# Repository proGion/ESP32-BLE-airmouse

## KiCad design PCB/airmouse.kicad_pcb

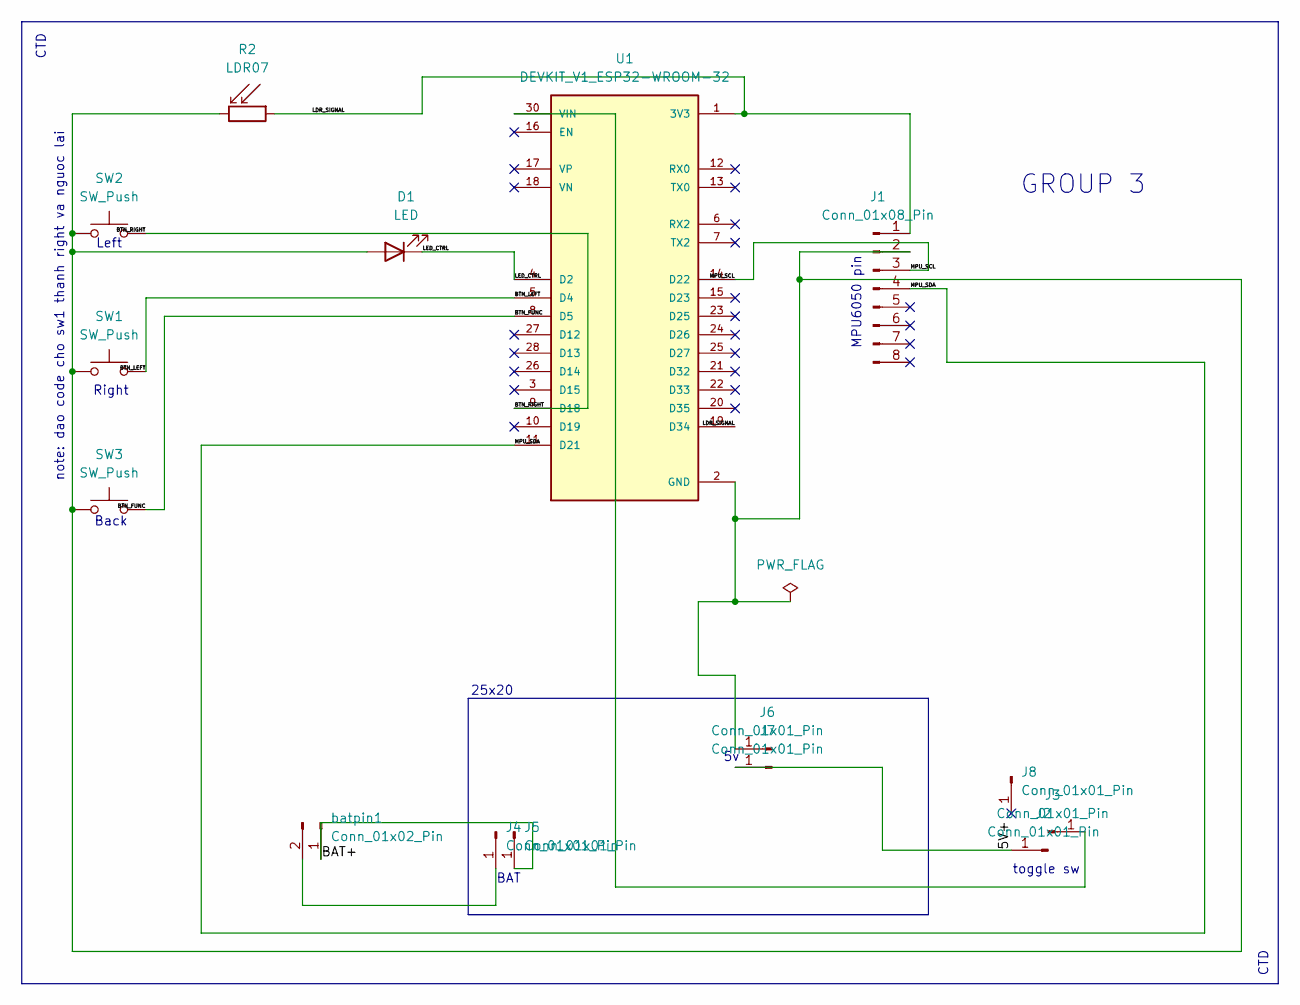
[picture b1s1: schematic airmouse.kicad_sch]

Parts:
D1: LED; LED_D5.0mm
J1: Conn_01x08_Pin; PinHeader_1x08_P2.54mm_Vertical
J2, J3, J4, J5, J6, J7, J8: Conn_01x01_Pin; PinHeader_1x01_P2.54mm_Vertical
R2: LDR07; R_LDR_5.1x4.3mm_P3.4mm_Vertical
SW1, SW2, SW3: SW_Push; SW_PUSH_6mm_H9.5mm
U1: DEVKIT_V1_ESP32-WROOM-32; MODULE_DEVKIT_V1_ESP32-WROOM-32
batpin1: Conn_01x02_Pin; PinHeader_1x02_P2.54mm_Vertical

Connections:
/5V+: J2.1 (Pin_1_1), J7.1 (Pin_1_1)
/BAT+: J5.1 (Pin_1_1), batpin1.1
/BTN_FUNC: SW3.2, U1.8 (D5)
/BTN_LEFT: SW1.2, U1.5 (D4)
/BTN_RIGHT: SW2.2, U1.9 (D18)
/LDR_SIGNAL: J1.1, R2.1, U1.1 (3V3), U1.19 (D34)
/LED_CTRL: D1.1 (K), U1.4 (D2)
/MPU_SCL: J1.3, U1.14 (D22)
/MPU_SDA: J1.4, U1.11 (D21)
GND: D1.2 (A), J1.2, J6.1 (Pin_1_1), R2.2, SW1.1, SW2.1, SW3.1, U1.2 (GND), U1.29 (GND)
unnamed: J3.1 (Pin_1_1), U1.30 (VIN)
unnamed: J4.1 (Pin_1_1), batpin1.2

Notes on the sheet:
MPU6050 pin
Left
CTD
note: dao code cho sw1 thanh right va nguoc lai
BAT
25x20
toggle sw
Right
GROUP 3
Back

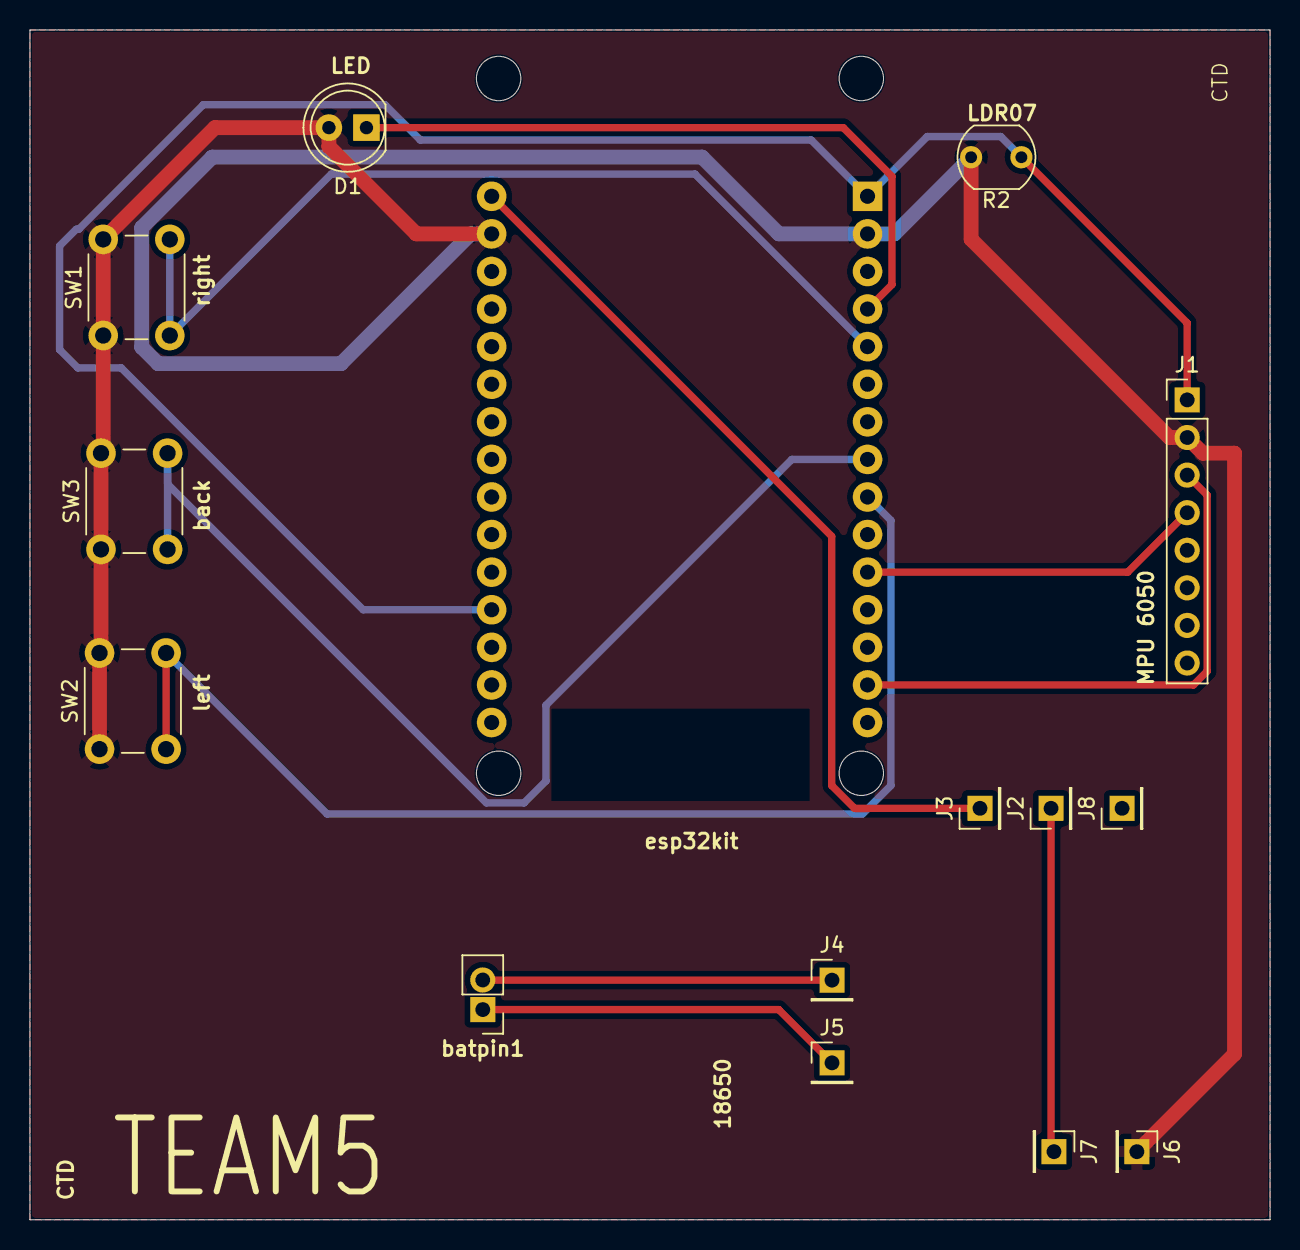
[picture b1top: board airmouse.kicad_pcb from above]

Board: 2 copper layers, 83.8 x 80.4 mm, 15 parts (1 on the bottom side), 12 nets.
